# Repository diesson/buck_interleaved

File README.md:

# buck_interleaved
Buck Interleaved

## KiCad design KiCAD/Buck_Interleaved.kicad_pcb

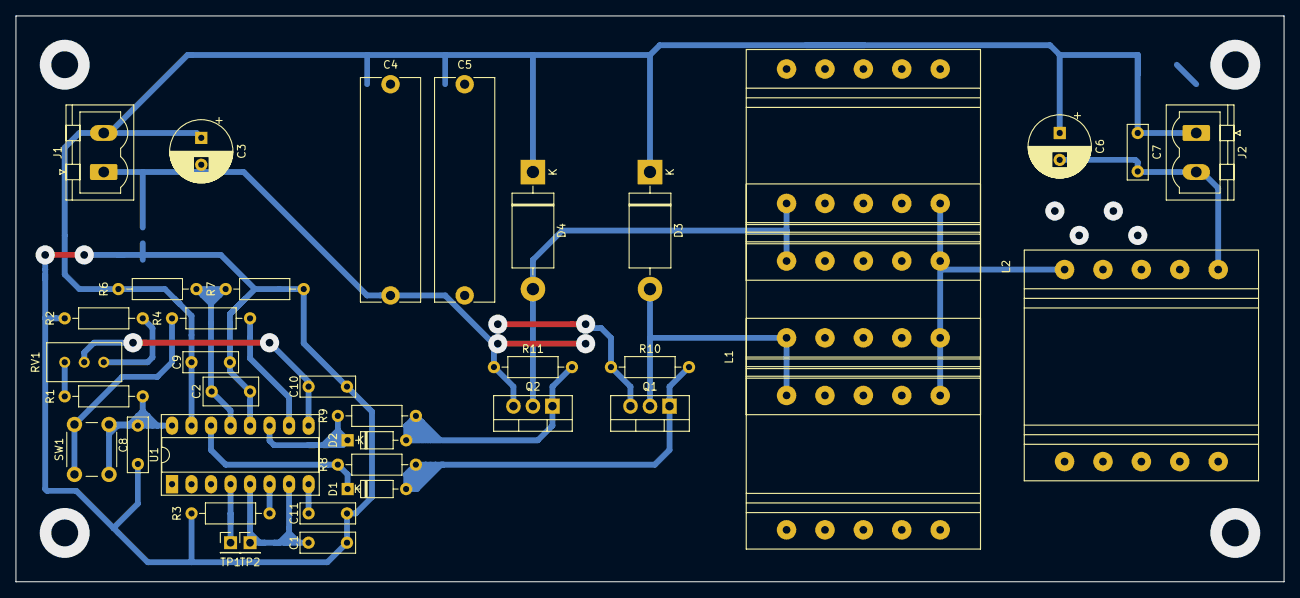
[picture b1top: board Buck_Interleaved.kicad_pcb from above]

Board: 2 copper layers, 165.1 x 73.7 mm, 37 parts (1 on the bottom side), 22 nets.

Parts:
C1, C8, C10: 10nF; C_Rect_L7.0mm_W2.5mm_P5.00mm
C2: 470nF; C_Rect_L7.0mm_W3.5mm_P5.00mm
C3, C6: 100uF; CP_Radial_D8.0mm_P3.50mm
C4, C5: 1uF; C_Rect_L29.0mm_W7.6mm_P27.50mm_MKT
C7, C9: 100nF; C_Rect_L7.0mm_W2.5mm_P5.00mm
C11: 1uF; C_Rect_L7.0mm_W2.5mm_P5.00mm
D1, D2: 1N4148; D_DO-35_SOD27_P7.62mm_Horizontal
D3, D4: MUR460; D_DO-201AD_P15.24mm_Horizontal
J1: Vi; PhoenixContact_MSTBVA_2,5_2-G-5,08_1x02_P5.08mm_Vertical
J2: Vo; PhoenixContact_MSTBVA_2,5_2-G-5,08_1x02_P5.08mm_Vertical
L1: array_indutor; Ind_Carretel_E30_15_7_2
L2: indutor_u; Ind_Carretel_E30_15_7
Q1, Q2: IRF540N; TO-220-3_Vertical
R1, R2: R_US; R_Axial_DIN0207_L6.3mm_D2.5mm_P10.16mm_Horizontal
R3: 1k2; R_Axial_DIN0207_L6.3mm_D2.5mm_P10.16mm_Horizontal
R4, R7: 2k; R_Axial_DIN0207_L6.3mm_D2.5mm_P10.16mm_Horizontal
R6: 820; R_Axial_DIN0207_L6.3mm_D2.5mm_P10.16mm_Horizontal
R8, R9: 22; R_Axial_DIN0207_L6.3mm_D2.5mm_P10.16mm_Horizontal
R10, R11: 10k; R_Axial_DIN0207_L6.3mm_D2.5mm_P10.16mm_Horizontal
R12: 0R; R_0805_2012Metric_Pad1.15x1.40mm_HandSolder
RV1: 10k; Potentiometer_Bourns_3296W_Vertical
SW1: SW_Push; SW_PUSH_6mm_H5mm
TP1, TP2: TestPoint; PinHeader_1x01_P2.54mm_Vertical
U1: SG3525; DIP-16_W7.62mm_Socket_LongPads

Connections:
+24V: C3.1, C4.1, C5.1, C6.1, C7.1, C9.1, D3.1, D4.1, J1.2, J2.1, R6.1, U1.15
GNDA: C1.2, C2.1, C8.2, C9.2, C10.2, C11.2, R2.1, R3.1, R7.2, R12.2, U1.12
GNDPWR: C3.2, C4.2, C5.2, J1.1, Q1.3, Q2.3, R10.1, R11.1, R12.1
unnamed: C1.1, TP2.1, U1.5, U1.7
unnamed: C2.2, R6.2, R7.1, U1.13
unnamed: C6.2, C7.2, J2.2, L2.4, L2.5
unnamed: C8.1, R1.2, SW1.2, U1.16
unnamed: C10.1, RV1.2, U1.9
unnamed: C11.1, U1.8
unnamed: D1.1, R8.1, U1.14
unnamed: D1.2, Q1.1, R8.2, R10.2
unnamed: D2.1, R9.1, U1.11
unnamed: D2.2, Q2.1, R9.2, R11.2
unnamed: D3.2, L1.1, L1.2, Q1.2
unnamed: D4.2, L1.9, L1.10, Q2.2
unnamed: L1.4, L1.5, L1.6, L1.7, L2.1, L2.2
unnamed: R1.1, RV1.1
unnamed: R2.2, RV1.3
unnamed: R3.2, U1.6
unnamed: R4.1, U1.10
unnamed: R4.2, SW1.1
unnamed: TP1.1, U1.4

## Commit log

2020-03-29 Add arquivos
